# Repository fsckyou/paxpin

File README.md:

# PAX pins
## Wots all this then?
Dude, I wanted to make some kickass pins to have and trade at PAX East 2020. So, being an electrical engineer, I went the super nerdy route and made the pins using PCBs. You have stumbled across my designs.

## Can I rip this off for myself?
Yeah. Sure. They're inspired by games I didn't make, so I think that's fair.

## Do you sell these?
Nope.

## Will there be more pin designs?
Most definitely.

## How do I make one?
Well, load this up in KiCad and make whatever modifications you want. Then export the drill and Gerber files and send them over to a board fab house. I recommend using http://jlcpcb.com . When you get the boards in hand, program the ATTiny (if the design has one) and assemble the boards. Then attach a pin back using superglue wherever you think it makes sense.

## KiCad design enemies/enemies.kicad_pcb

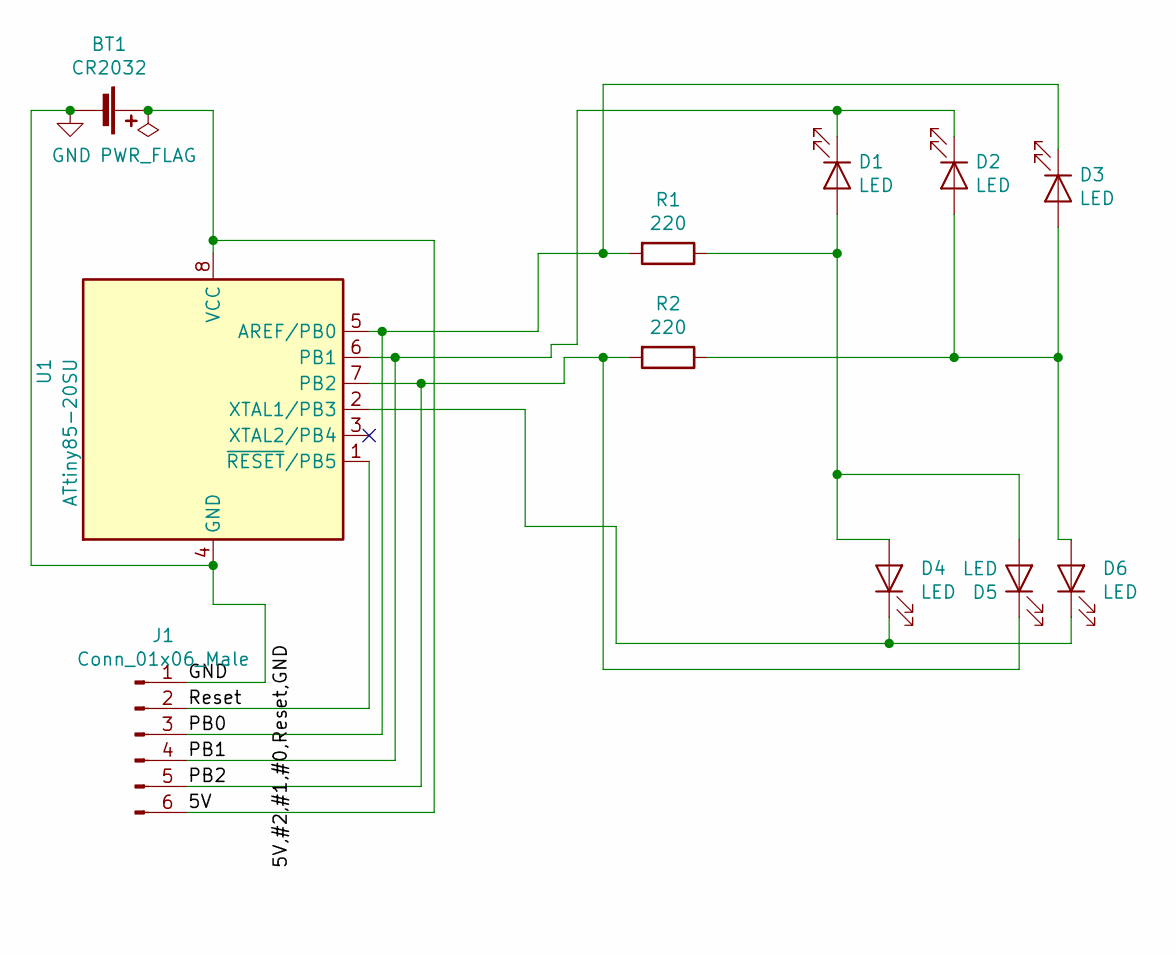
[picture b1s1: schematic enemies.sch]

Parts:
BT1: CR2032; BatteryHolder_Keystone_3002_1x2032
D1, D2, D3, D4, D5, D6: LED; LED_0805_2012Metric
J1: Conn_01x06_Male; PinHeader_1x06_P2.54mm_Vertical
R1, R2: 220; R_0603_1608Metric
U1: ATtiny85-20SU; SOIJ-8_5.3x5.3mm_P1.27mm

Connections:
/5V: BT1.1 (+), J1.6, U1.8 (VCC)
/PB0: D3.1 (K), J1.3, R1.2, U1.5 (AREF/PB0)
/PB1: D1.1 (K), D2.1 (K), J1.4, U1.6 (PB1)
/PB2: D5.1 (K), J1.5, R2.2, U1.7 (PB2)
/Reset: J1.2, U1.1 (~RESET~/PB5)
GND: BT1.2 (-), J1.1, U1.4 (GND)
unnamed: D1.2 (A), D4.2 (A), D5.2 (A), R1.1
unnamed: D2.2 (A), D3.2 (A), D6.2 (A), R2.1
unnamed: D4.1 (K), D6.1 (K), U1.2 (XTAL1/PB3)

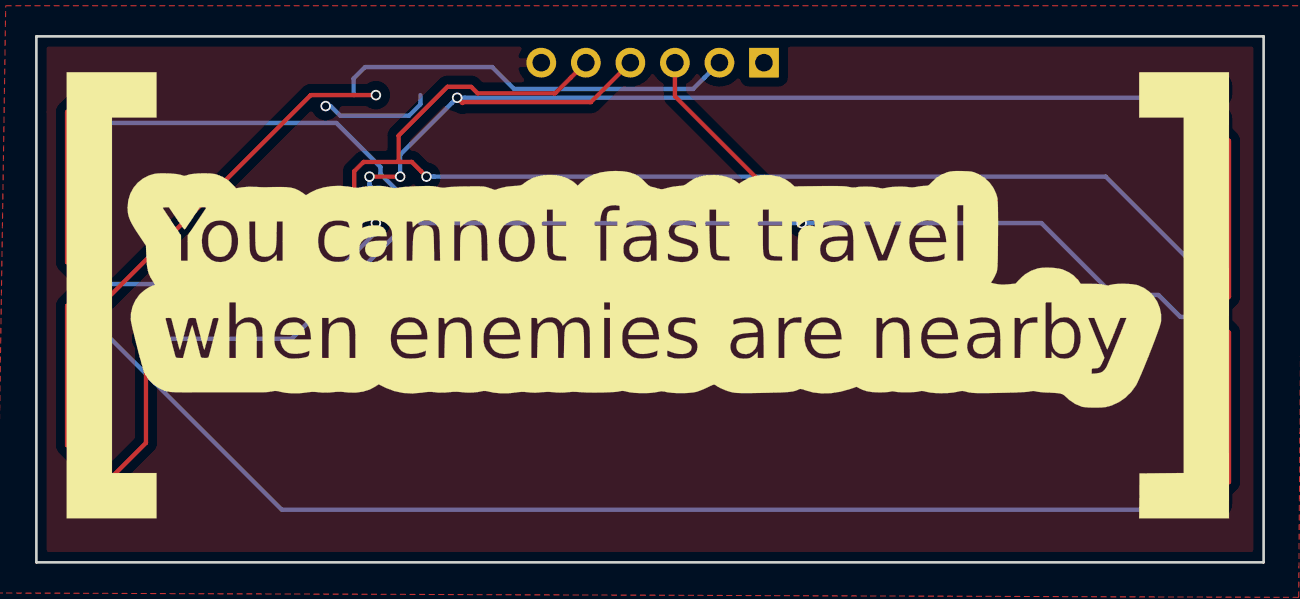
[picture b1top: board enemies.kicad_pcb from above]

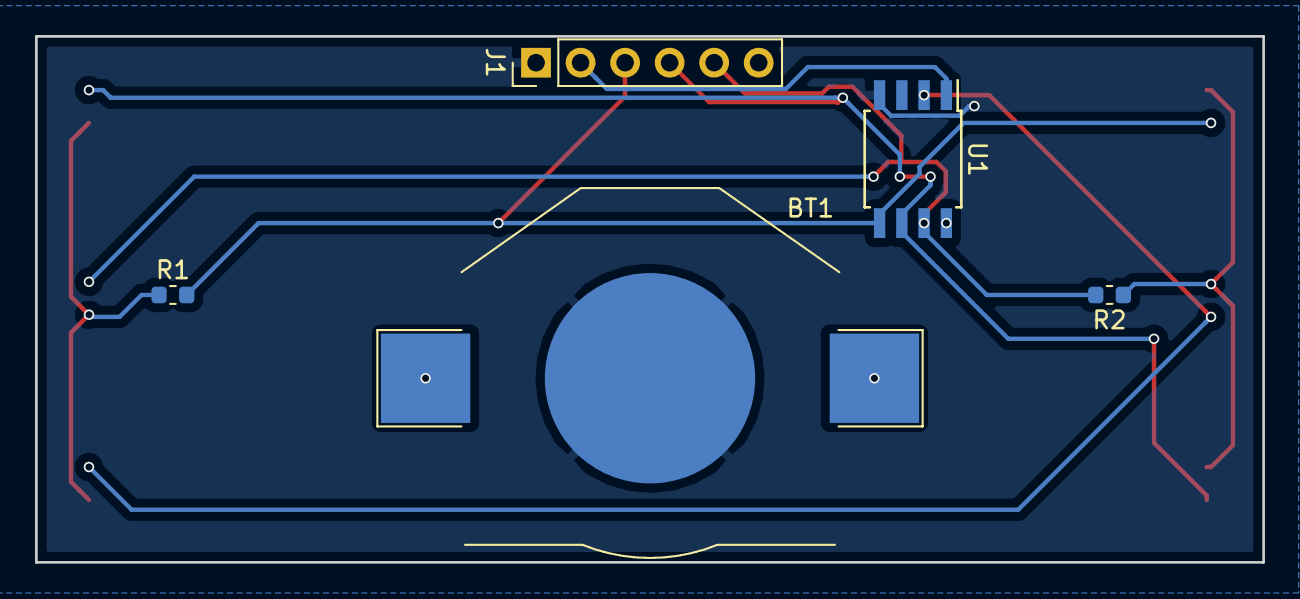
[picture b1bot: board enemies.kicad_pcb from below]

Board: 2 copper layers, 70.0 x 30.0 mm, 11 parts (5 on the bottom side), 9 nets.

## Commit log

2020-02-16 As fabricated
2020-02-16 get rid of silly cache thing
2020-02-16 somehow the schematic for uradisappointment disappeared
